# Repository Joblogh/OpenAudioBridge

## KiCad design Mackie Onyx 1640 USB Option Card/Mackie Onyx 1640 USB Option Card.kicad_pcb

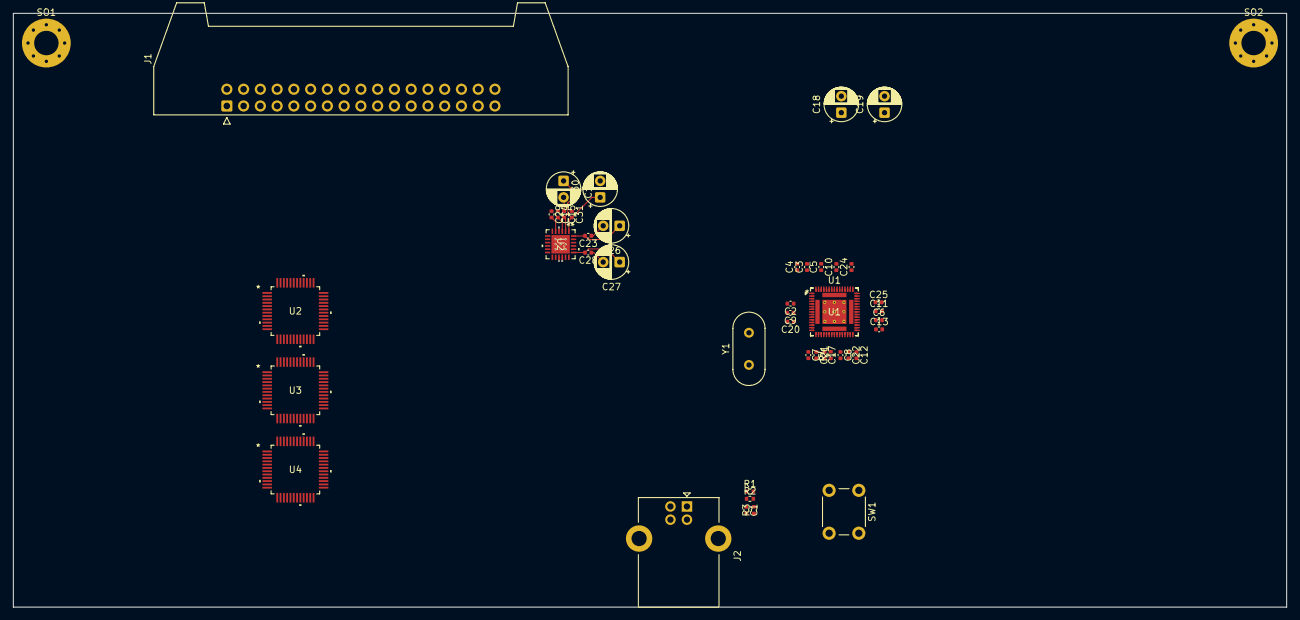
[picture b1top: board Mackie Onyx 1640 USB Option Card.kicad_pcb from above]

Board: 2 copper layers, 193.0 x 90.0 mm, 47 parts (0 on the bottom side), 20 nets.

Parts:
C1: 2u2C; C_0402_1005Metric
C2, C3, C4, C5, C6, C7, C8, C9, C10, C11, C12, C13, C15, C20, C21, C22, C23, C24, C25, C28, C31: 100nC; C_0402_1005Metric
C14, C17, C29: 1uC; C_0402_1005Metric
C16, C18, C19, C26, C27, C30: 10uC_Polarized; CP_Radial_D5.0mm_P2.50mm
J1: Conn_02x17_Odd_Even; IDC-Header_2x17_P2.54mm_Latch_Horizontal
J2: USB_B; USB_B_Lumberg_2411_02_Horizontal
R1: 47kR; R_0402_1005Metric
R2: 220kR; R_0402_1005Metric
R3: 330kR; R_0402_1005Metric
R4: 600R@100Mhz; R_0402_1005Metric
SO1, SO2: MountingHole_3.7mm_Pad_Via
SW1: SW_Push; SW_PUSH_6mm
U1: XU316-1024-QF60B-C24; QFN-60-1EP_7x7mm_P0.4mm_EP3.4x3.4mm_ThermalVias
U1#2: XU316-1024-QF60B-C24; QFN_F60B-C24_XMO
U2, U3, U4: CS5368-CQZ; CIR-LQFP-48
U2#2: TLV320ADC5140IRTWR; RTW24_4P15X4P15_TEX
Y1: 24MHz Crystal; Crystal_HC49-U_Vertical

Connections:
+5V: J1.32, J1.33, J1.34
+15V: J1.25, J1.26
-15V: J1.27, J1.28
/USB Connector/D+: J2.3 (D+), U1.29 (USB_DP)
/USB Connector/D-: J2.2 (D-), U1.28 (USB_DM)
/USB Connector/Detect: R2.2, R3.2
ADV1_AREG: C15.2, C16.1, U2#2.2 (AREG)
ADV1_AVDD: C9.1, C10.1, C11.1, C12.1, C27.1, C28.2, C30.1, C31.2, U1.8 (VDDIOL), U1.30 (USB_VDD33), U1.38 (VDDIOR), U1.52 (VDDIOT), U2#2.1 (AVDD), U2#2.19 (IOVDD)
ADV1_DREG: C23.2, C26.1, U2#2.24 (DREG)
ADV1_MICBIAS: C29.2, U2#2.5 (MICBIAS)
ADV1_VREF: C14.2, U2#2.3 (VREF)
Earth: J1.29, J1.30, J1.31, J2.5 (Shield)
GND: C1.2, C2.2, C3.2, C4.2, C5.2, C6.2, C7.2, C8.2, C9.2, C10.2, C11.2, C12.2, C13.2, C14.1, C15.1, C16.2, C17.2, C18.2, C19.2, C20.2, C21.2, C22.2, C23.1, C24.2, C25.2, C26.2, C27.2, C28.1, C29.1, C30.2, C31.1, J1.17, J1.18, J1.21, J1.22, J2.4 (GND), R1.2, R3.1, SW1.1, U2#2.4 (AVSS), U2#2.15 (ADDR1_MISO), U2#2.16 (ADDR0_SCLK), U2#2.25 (EPAD)
MCU_PLL_AVDD: C17.1, R4.2, U1.22 (PLL_AVDD)
MCU_USB_VDD1V8: C7.1, C8.1, C13.1, C19.1, U1.17 (VDDIOB18), U1.26 (VDDIOB18), U1.31 (USB_VDD18)
MCU_VDD1: C2.1, C3.1, C4.1, C5.1, C6.1, C18.1, C20.1, C21.1, C22.1, C24.1, C25.1, R4.1, U1.4 (VDD), U1.12 (VDD), U1.19 (VDD), U1.27 (VDD), U1.34 (VDD), U1.42 (VDD), U1.49 (VDD), U1.57 (VDD), U1.61 (VDD)
unnamed: C1.1, J2.1 (VBUS), R1.1, R2.1
unnamed: SW1.2, U1.21 (RST_N)
unnamed: U1.16 (XIN), Y1.1
unnamed: U1.15 (XOUT), Y1.2
